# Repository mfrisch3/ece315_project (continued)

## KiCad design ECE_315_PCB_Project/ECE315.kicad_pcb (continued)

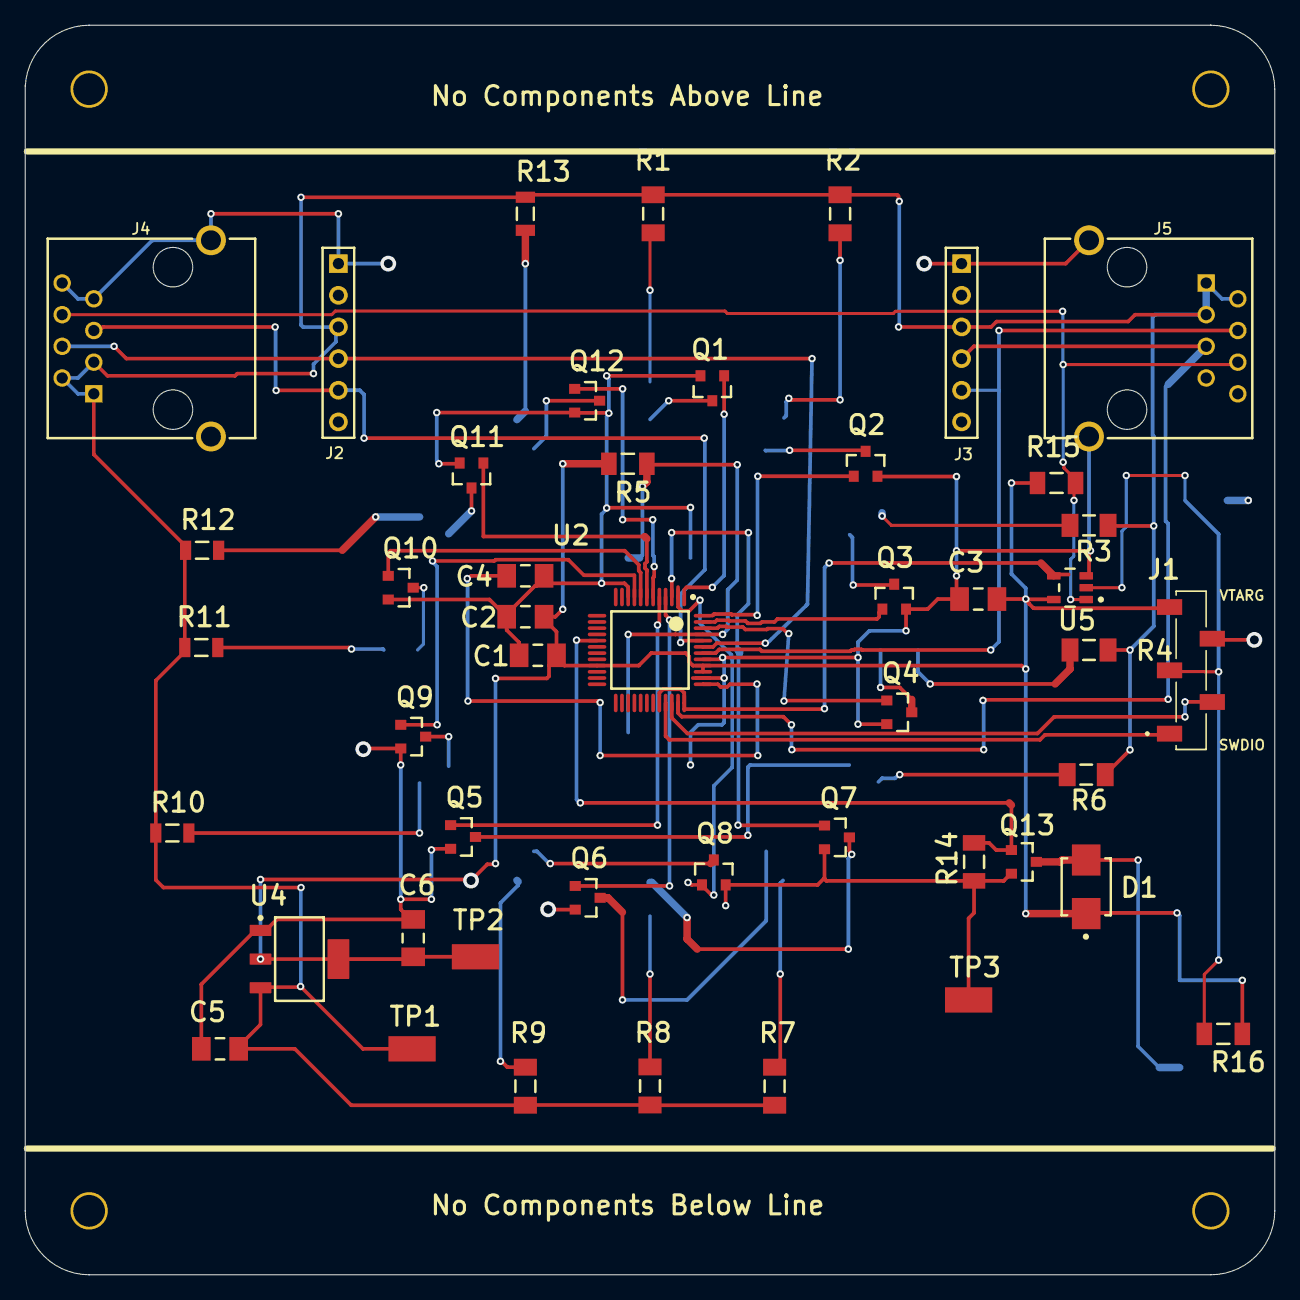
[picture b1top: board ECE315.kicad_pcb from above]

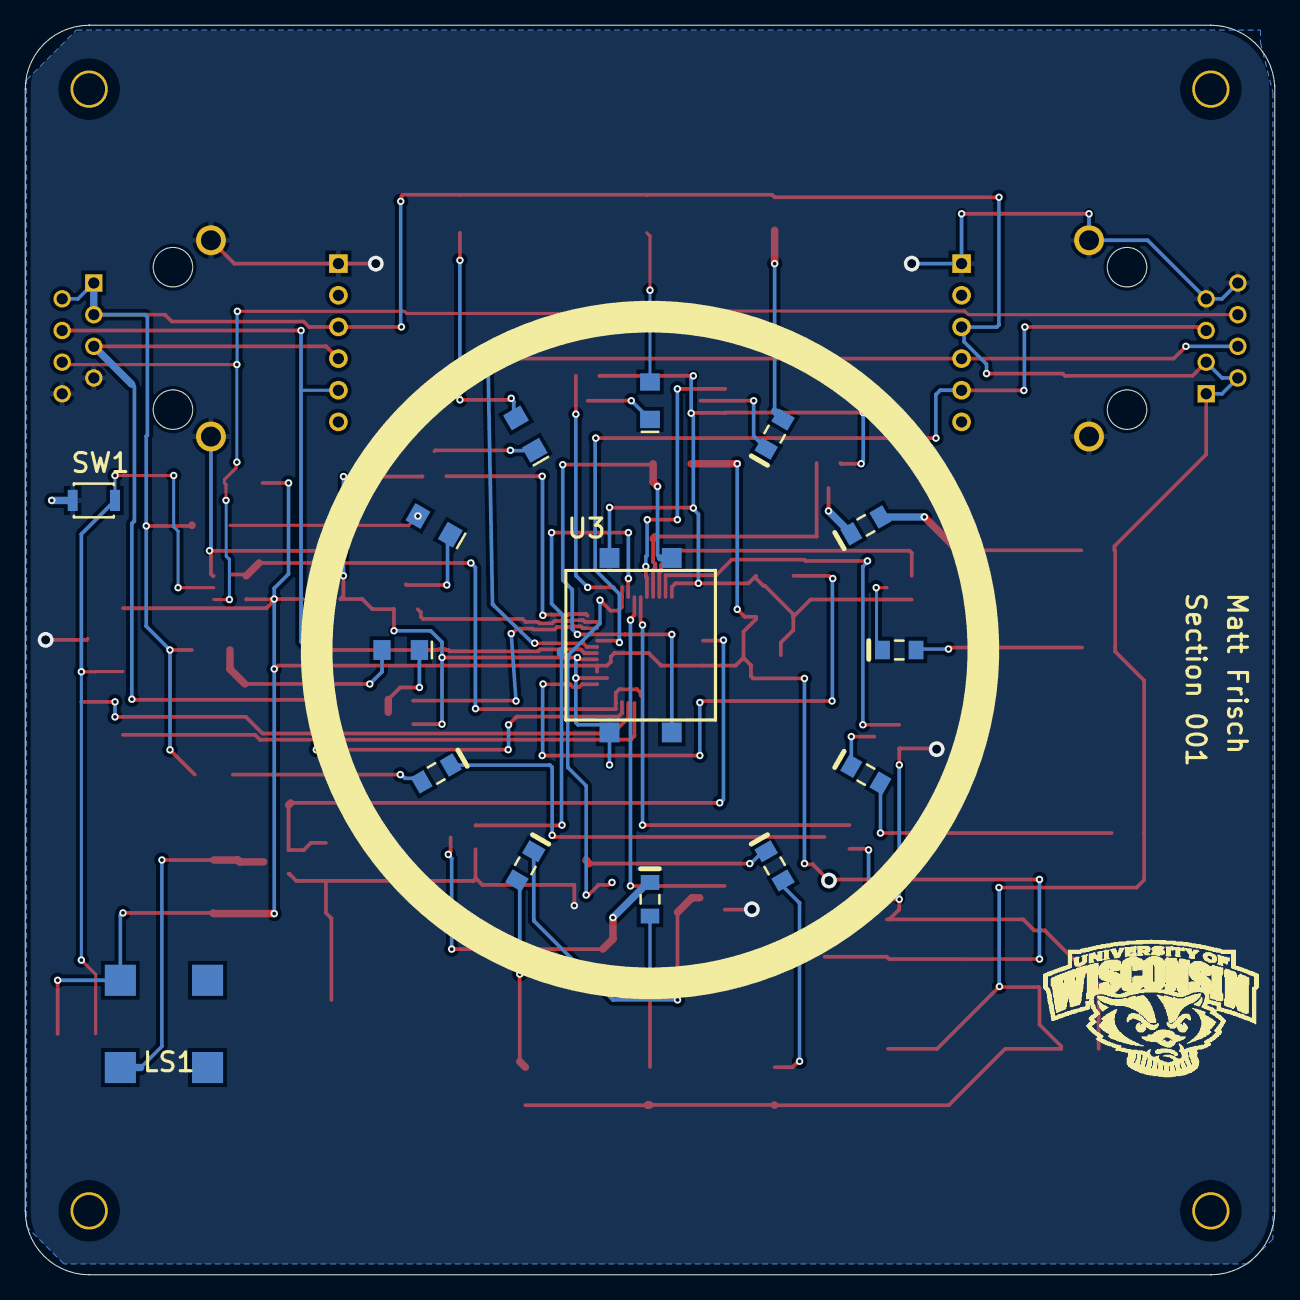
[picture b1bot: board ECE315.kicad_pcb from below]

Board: 2 copper layers, 100.3 x 100.3 mm, 67 parts (16 on the bottom side), 52 nets.

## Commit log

2023-11-27 Initial Project Creation
2023-11-27 Removing interrupts.c and .h files
2025-09-01 updated main.c
2025-09-01 added pcb files
